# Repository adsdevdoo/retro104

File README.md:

# retro104

Платы расширения **PC/104** (шина ISA 8/16 бит) для ретро-одноплатников. Первый хост —
Advantech **PCM-3860/64 Rev.A1** с видеоконтроллером C&T F65545, то есть вариант **PCM-3864**
(386SX-40, плата 145 × 102 мм с разъёмами PC/104 CN1/CN2).

| pc104-audio — звуковая карта | pc104-blank — механическая ответка |
|---|---|
|  |  |

| Этап | Плата | Состояние |
|---|---|---|
| 1 | [`pc104-blank`](hardware/pc104-blank/) — пустая механическая ответка | **rev A: ERC 0, DRC 0, контакты сверены 104/104, Gerber проверены. Не изготовлена** |
| 2 | [`pc104-audio`](hardware/pc104-audio/) — звуковая карта на ESS ES1868F (донор BTC 1853L) | **rev A: ERC 0, нетлист сверен, разведена, DRC 0, Gerber проверены. Не изготовлена** |
| 3 | Ethernet | не начата |

**Статус: инженерные прототипы, не изготавливались и в железе не проверялись.**
Заказ, оплату и загрузку файлов в JLCPCB выполняет владелец. Изменения плат по ревизиям —
[CHANGELOG.md](CHANGELOG.md).

## pc104-audio — звуковая карта

Модуль PC/104 16 бит на **ESS ES1868F** с донорской карты BTC 1853L: Sound Blaster Pro 3.01,
FM-синтез ESFM (совместим с OPL3 по регистрам), MPU-401 UART и game port. Схема повторяет типовое
включение ESS (даташит ES1868, прил. B) с решениями владельца ([audio-options.md](docs/audio-options.md)).

- **Звук:** линейный выход, линейный вход, микрофон — гнёзда 3.5 мм Same Sky SJ1-3523N на верхнем
  крае, который при установке смотрит в сторону COM1 хоста. Усилителя нет.
- **Game/MIDI:** угловой IDC 2 × 8 на нижнем крае под стандартный кабель с планкой DB-15
  (раскладка National AN-1130). Вертикальный разъём с кабелем не проходит по высоте PC/104.
- **С донора:** ES1868F, EEPROM 93C66 (в панели, данные PnP) и при желании 74LS138. Кварц
  14.31818 МГц — низкий HC-49/S; донорский HC-49/U ставится только лёжа.
- **Питание:** только +5 В шины, аналоговая часть — через феррит.

| ES1868 | IRQA | IRQB | IRQC | IRQD | IRQE | IRQF | DRQA | DRQB | DRQC | DRQD |
|---|---|---|---|---|---|---|---|---|---|---|
| Линия ISA | 9 | 5 | 7 | 10 | 11 | 12 | 0 | 1 | 3 | 5 |

Раскладка — как у ESS и в EEPROM типовых карт, поэтому 93C66 донора подходит без перепрошивки.
Рекомендуемые ресурсы на PCM-3864: SB 220h / IRQ5 / DMA1, MPU-401 330h, FM 388h, джойстик 201h;
LPT хоста — на IRQ7. Подробно — [docs/pc104-audio.md](docs/pc104-audio.md).

<details>
<summary>Низ платы: название, таблицы IRQ/DRQ и ресурсов, перемычки, выводы J4 на шелкографии</summary>

</details>

Плата 95.89 × 90.17 мм, 2 слоя. Сигналы 0.25 мм, питание 0.4 мм, земля залита с двух сторон и
сшита. Трассировка — FreeRouting 2.5.0. На шелкографии верха обозначения всех деталей, у микросхем,
кварца и электролитов — номиналы. Архив для заказа:
[hardware/pc104-audio/fabrication/](hardware/pc104-audio/fabrication/).

## pc104-blank — механическая ответка

Электрически пустой модуль PC/104: только площадки разъёмов CN1/CN2 и четыре крепёжных отверстия.
На нём проверяются габарит, отверстия, ориентация и сопряжение разъёмов с PCM-3864. Контур,
отверстия и CN1/CN2 звуковой карты взяты отсюда.

| Параметр | CN2 | CN1 |
|---|---|---|
| По стандарту PC/104 | J1/P1, ряды A/B, контакты 1–32 | J2/P2, ряды C/D, контакты 0–19 |
| На PCM-3864 (с. 67 руководства) | CN2, 64 контакта | CN1, 40 контактов («Row A/B» = C/D) |
| Разъём | Samtec **ESQ-132-39-G-D** | Samtec **ESQ-120-39-G-D** |
| Тип | проходной (stackthrough): гнездо сверху, штыри снизу | то же |
| Корпус над платой / штырь под корпусом | 11.05 мм / 12.19 мм, квадрат 0.64 мм | то же |
| Отверстие / площадка | 1.02 мм (Samtec ESQ-SDT) / 1.70 мм | то же |
| Pin 1 (квадратная площадка, стрелка) | A1 | C0 |
| Положение, PC/104 рис. 3 | A: X 0.400 in, B: X 0.500 in; A1 в Y 0.250 in | C: X 0.300 in, D: X 0.200 in; C0 в Y 1.050 in |
| Ключевая позиция стандарта | B10 (у Advantech — GND) | C19 (у Advantech — N/C) |

Плата 3.775 × 3.550 in (95.89 × 90.17 мм), отверстия Ø3.18 мм с площадкой Ø6.35 мм:
(0.200; 0.200), (0.200; 3.350), (3.575; 0.350), (3.575; 3.250) in.

**Переходник не нужен.** Разъёмы PCM-3864 — гнёзда (руководство с. 58–59), а у модулей retro104 снизу
штыри проходных разъёмов. Переходник «male-male» Advantech нужен только модулю, у которого снизу тоже
гнёзда. Конец разъёмов с pin 32 / pin 19 при установке смотрит в сторону COM1 хоста.

| Верх | Сопряжение с гнёздами хоста (иллюстративные модели) |
|---|---|
|  |  |

## Документация

| Файл | Что внутри |
|---|---|
| [docs/pc104-audio.md](docs/pc104-audio.md) | звуковая карта: схема, IRQ/DMA, разъём game/MIDI, проверки, первая настройка |
| [docs/audio-options.md](docs/audio-options.md) | варианты звуковой карты, донор BTC 1853L, решения владельца |
| [docs/pc104-audio-schematic.pdf](docs/pc104-audio-schematic.pdf), [docs/pc104-audio-assembly.pdf](docs/pc104-audio-assembly.pdf) | схема и сборочный чертёж звуковой карты |
| [docs/mechanics.md](docs/mechanics.md) | механика PC/104 со ссылками на страницы, неоднозначности руководства, сверка с фото, переходник |
| [hardware/pc104-blank/reports/pinout-check.md](hardware/pc104-blank/reports/pinout-check.md) | все 104 контакта: координаты, PC/104 v2.6 и Advantech |
| [docs/pc104-blank-schematic.pdf](docs/pc104-blank-schematic.pdf) | схема ответки (все выводы не подключены) |
| [docs/manufacturing.md](docs/manufacturing.md) | заказ обеих плат в JLCPCB, что проверено и что нет |
| [docs/models.md](docs/models.md) | 3D-модели и их ограничения |
| [docs/sources.md](docs/sources.md) | документы, фото, открытые проекты, лицензионные пометки |
| [CHANGELOG.md](CHANGELOG.md) | изменения плат по ревизиям: медь, шелкография, файлы производства |

Документы производителей лежат в [docs/datasheets/](docs/datasheets/), фото хоста и донора — в
[docs/references/photos/](docs/references/photos/).

## Открыть и пересобрать

Нужен **KiCad 9.0.2 или новее**. Проекты: `hardware/pc104-audio/pc104-audio.kicad_pro` и
`hardware/pc104-blank/pc104-blank.kicad_pro`. Символы, футпринты и 3D-модели общие: `hardware/lib/`.

Схемы, платы, отчёты, рендеры, Gerber и проверки генерируются скриптами:

```bash
python tools/make_all.py
```

Без флагов звуковая карта не перетрассируется: разводка FreeRouting от запуска к запуску может
отличаться. Полная перестройка с FreeRouting 2.5.0 (jar лежит вне репозитория, `../tools/`):

```bash
python tools/make_all.py --route-audio
```

- Механика и таблицы сигналов PC/104 — `tools/pc104_data.py`, у каждой цифры ссылка на страницу.
- Детали и цепи звуковой карты — `tools/audio_design.py`, из него строятся схема, плата и проверки.
- Независимые проверки плат и файлов производства — `tools/check_board.py`,
  `tools/check_audio_netlist.py`, `tools/check_audio_board.py`.

## Структура

```
docs/        документация, datasheets/, references/photos/
hardware/    lib/ (общие символы, футпринты, 3D), pc104-blank/, pc104-audio/ (проекты, reports/, fabrication/)
images/      CAD-рендеры
tools/       генераторы и проверки
```

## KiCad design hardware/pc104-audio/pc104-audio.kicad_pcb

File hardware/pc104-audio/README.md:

# pc104-audio rev A

Звуковая карта PC/104 на ESS ES1868F (этап 2). Описание схемы, ресурсов и разъёмов —
[docs/pc104-audio.md](../../docs/pc104-audio.md). Проект для **KiCad 9.0.2 или новее**:
откройте `pc104-audio.kicad_pro`.

| Файл | Что это |
|---|---|
| `pc104-audio.kicad_sch` | схема, один лист A2: каждый вывод с меткой цепи, неиспользуемые — с флагом NC |
| `pc104-audio.kicad_pcb` | плата 95.89 × 90.17 мм, 2 слоя, разведена FreeRouting 2.5.0, GND залит с двух сторон |
| `../lib/` | общая библиотека: символы, футпринты (свои и копии KiCad 9), 3D-модели |
| `reports/erc.rpt`, `reports/drc.rpt` | ERC и DRC с проверкой соответствия схеме |
| `reports/netlist-check.txt` | нетлист против `tools/audio_design.py` |
| `reports/fab-check.md` | контур, CN1/CN2 и отверстия по стандарту, сверловка против платы |
| `fabrication/` | Gerber, Excellon, карты сверловки, архив для JLCPCB, `SHA256SUMS` |
| `../../docs/pc104-audio-assembly.pdf` | сборочный чертёж: верхняя шелкография и слой F.Fab (контуры корпусов) |

Статус: **ERC 0; нетлист = `audio_design.py`; FreeRouting — 0 неразведённых; DRC 0 нарушений,
0 неподключённых, 0 ошибок футпринтов; файлы производства проверены. В железе не проверялась.**

Как получена плата:

1. `tools/audio_design.py` — детали, цепи и неподключённые выводы.
2. `tools/gen_audio.py` — схема; `kicad-cli sch export netlist` — нетлист.
3. `tools/check_audio_netlist.py` — нетлист против `audio_design.py`.
4. `tools/build_audio_board.py` — расстановка и DSN.
5. FreeRouting 2.5.0 — трассировка.
6. `tools/route_audio_board.py` — импорт трассировки, земля, сшивка.
7. `tools/audio_silk.py` — шелкография обеих сторон.

Всё это делает `python tools/make_all.py --route-audio`. Без флага плата не перетрассируется:
выполняется только шаг 7, затем проверки и выгрузка. Шаг 7 меняет только шелкографию и при повторном
запуске даёт тот же файл.

Шелкография:

- **Верх.** Обозначения всех деталей, 1.0 мм. У микросхем, кварца и электролитов указан номинал:
  ES1868F, 74HCT138, 93C66, 14.318MHz, 10u/47u. Место для подписи скрипт ищет сам: не ближе
  0.2 мм к площадкам и другой шелкографии, не на чужих корпусах, не ближе 0.5 мм к краю. Номиналы
  0805 — в схеме.
- **Низ.** Рамка с названием. Таблица соответствия линий IRQ/DRQ ES1868 линиям ISA. Типовые ресурсы
  PnP. Назначение перемычек JP1/JP2. Сведения о гнёздах. Названия выводов J4 у каждой площадки.
  Подписи CN1/CN2 и ссылка на репозиторий.

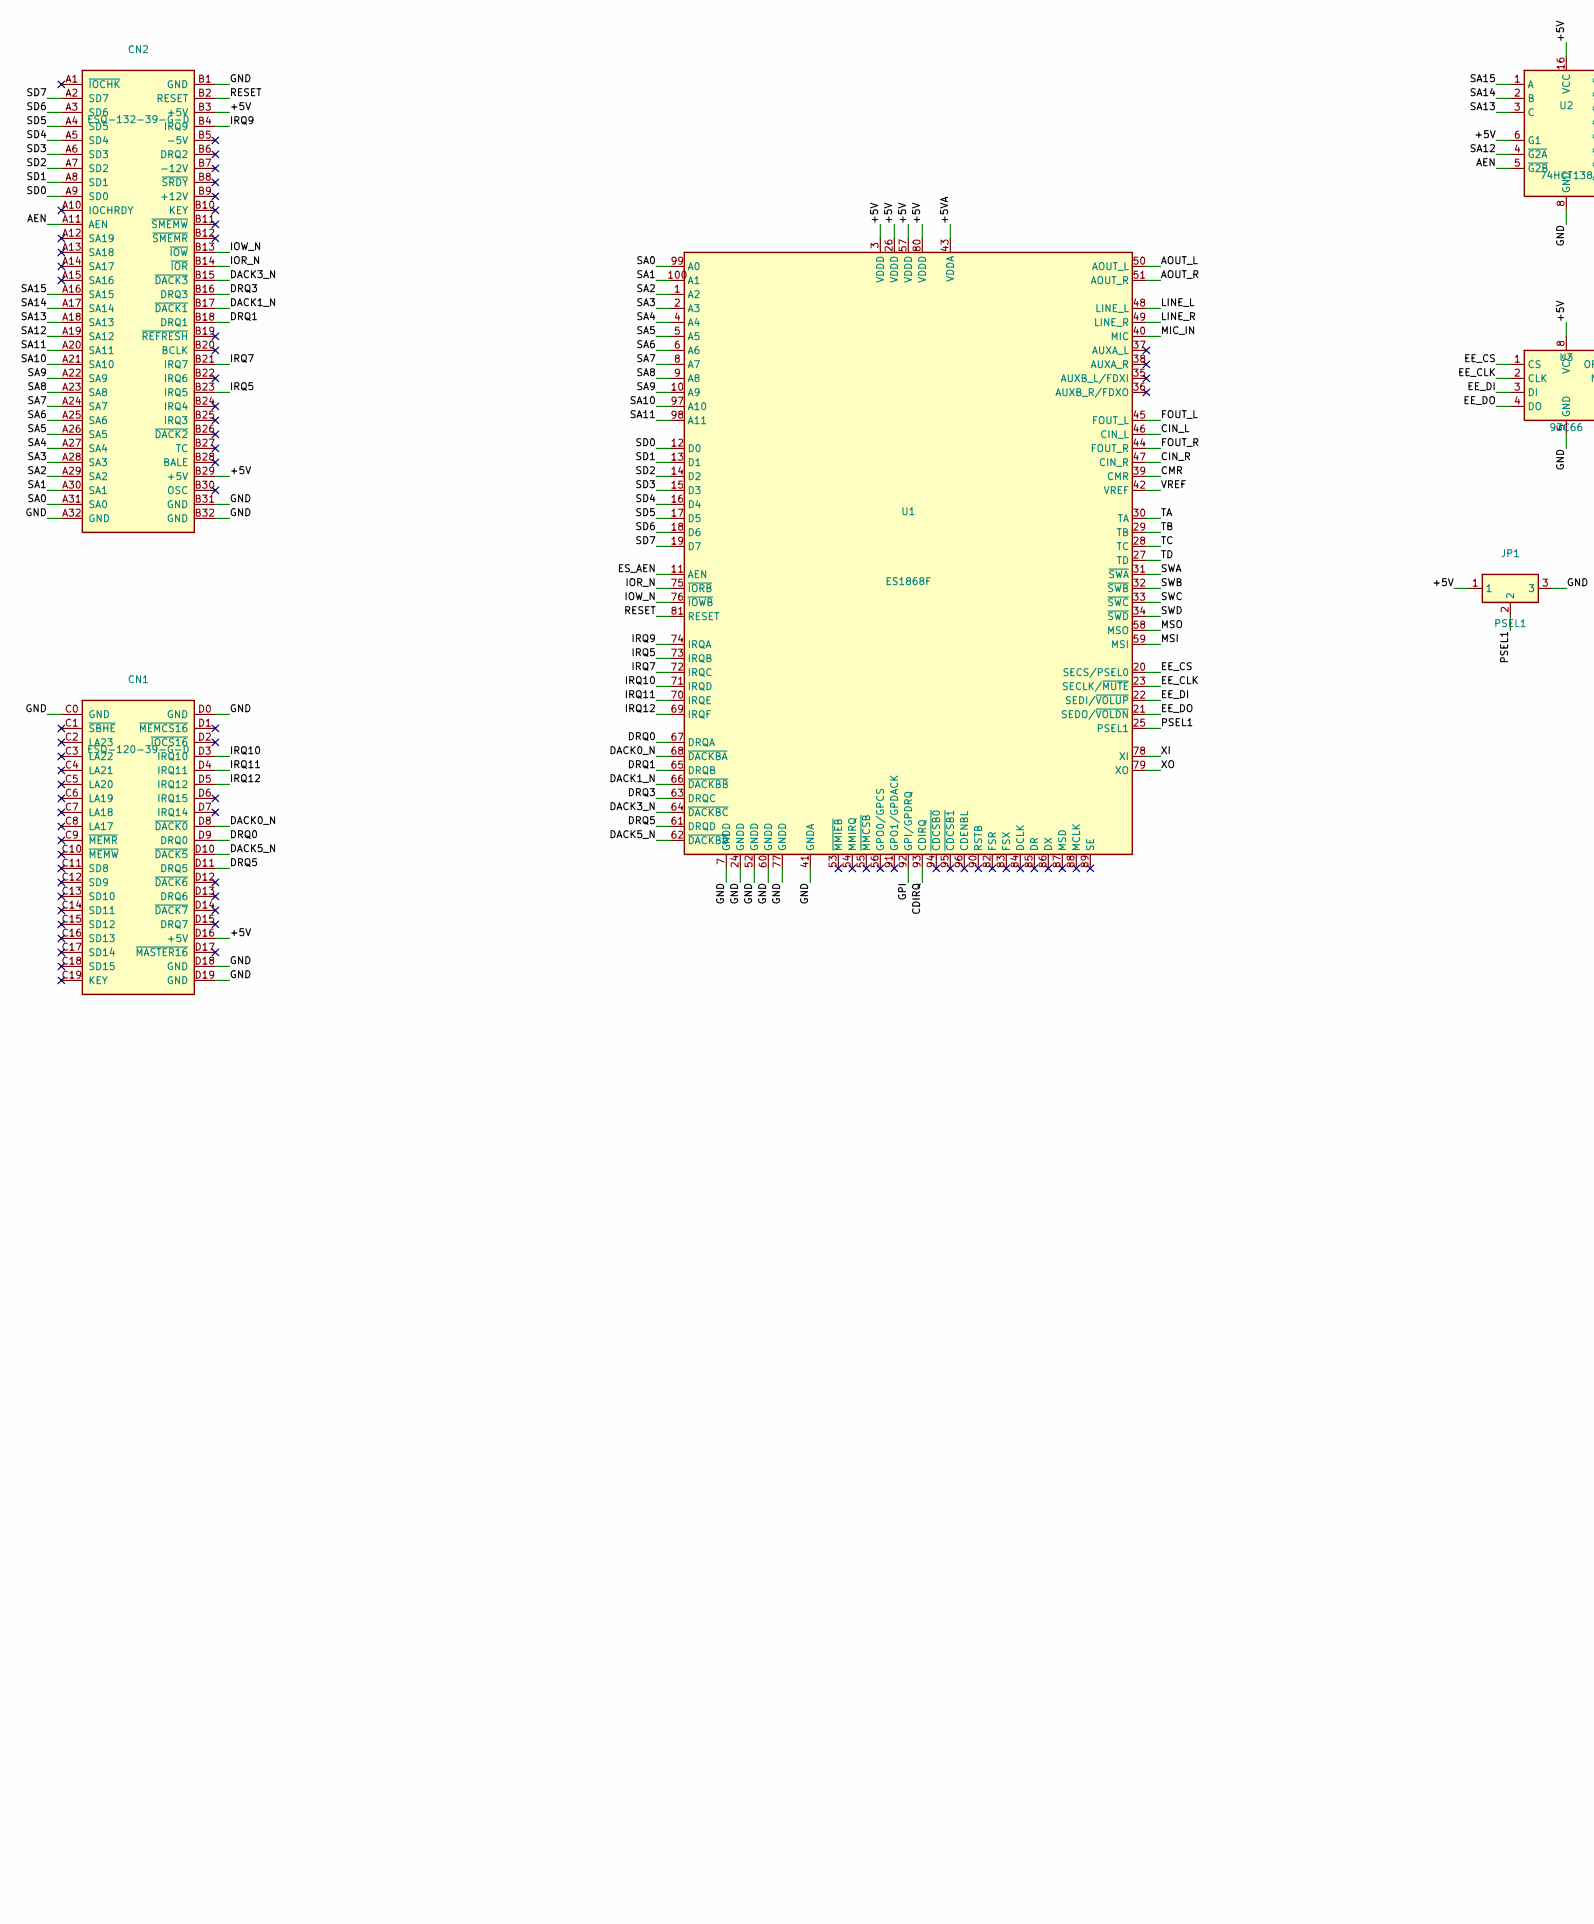
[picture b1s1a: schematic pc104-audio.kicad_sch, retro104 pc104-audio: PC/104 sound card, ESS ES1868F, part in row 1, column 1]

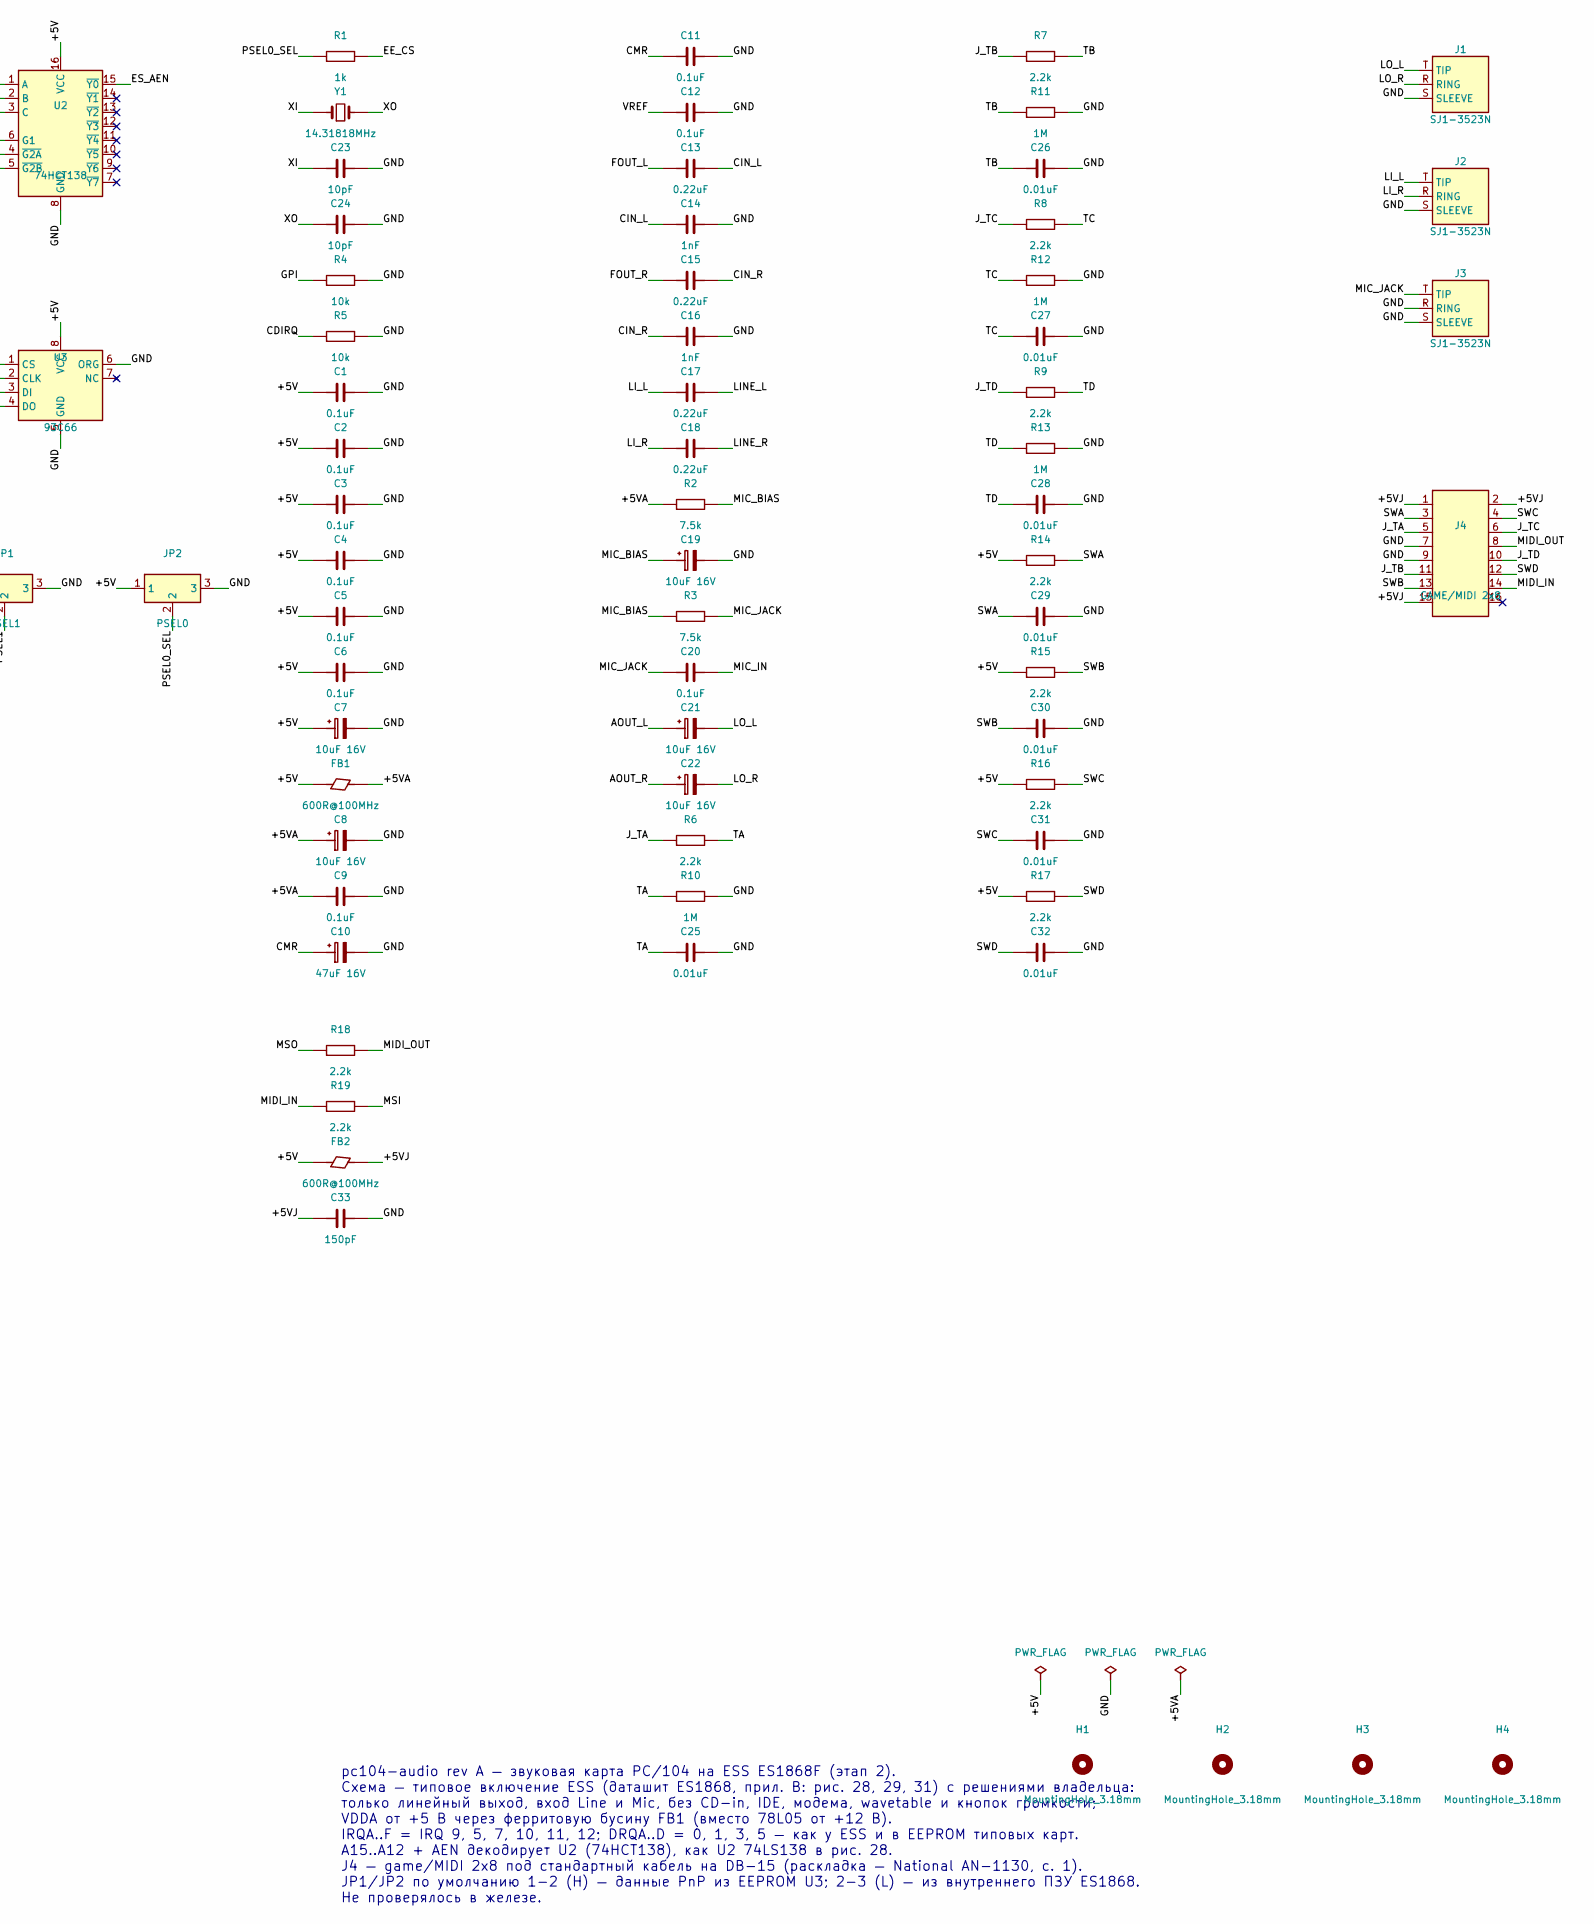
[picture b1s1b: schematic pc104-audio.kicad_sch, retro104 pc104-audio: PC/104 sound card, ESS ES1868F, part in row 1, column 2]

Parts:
C1, C2, C3, C4, C5, C6, C9, C11, C12, C20: 0.1uF; C_0805_2012Metric_Pad1.18x1.45mm_HandSolder
C7, C8, C19, C21, C22: 10uF 16V; CP_Elec_4x5.4
C10: 47uF 16V; CP_Elec_6.3x5.4
C13, C15, C17, C18: 0.22uF; C_0805_2012Metric_Pad1.18x1.45mm_HandSolder
C14, C16: 1nF; C_0805_2012Metric_Pad1.18x1.45mm_HandSolder
C23, C24: 10pF; C_0805_2012Metric_Pad1.18x1.45mm_HandSolder
C25, C26, C27, C28, C29, C30, C31, C32: 0.01uF; C_0805_2012Metric_Pad1.18x1.45mm_HandSolder
C33: 150pF; C_0805_2012Metric_Pad1.18x1.45mm_HandSolder
CN1: ESQ-120-39-G-D; PC104_J2P2_2x20_P2.54mm_Stackthrough; MPN Samtec ESQ-120-39-G-D
CN2: ESQ-132-39-G-D; PC104_J1P1_2x32_P2.54mm_Stackthrough; MPN Samtec ESQ-132-39-G-D
FB1, FB2: 600R@100MHz; L_0805_2012Metric_Pad1.15x1.40mm_HandSolder
H1, H2, H3, H4: MountingHole_3.18mm; PC104_MountingHole_3.18mm_Pad6.35mm
J1, J2, J3: SJ1-3523N; Jack_3.5mm_CUI_SJ1-3523N_Horizontal_Slots; MPN CUI/Same Sky SJ1-3523N
J4: GAME/MIDI 2x8; IDC-Header_2x08_P2.54mm_Horizontal; MPN 2x8 IDC box header, right angle, 2.54 mm
JP1: PSEL1; SolderJumper-3_P1.3mm_Bridged12_RoundedPad1.0x1.5mm
JP2: PSEL0; SolderJumper-3_P1.3mm_Bridged12_RoundedPad1.0x1.5mm
R1: 1k; R_0805_2012Metric_Pad1.20x1.40mm_HandSolder
R2, R3: 7.5k; R_0805_2012Metric_Pad1.20x1.40mm_HandSolder
R4, R5: 10k; R_0805_2012Metric_Pad1.20x1.40mm_HandSolder
R6, R7, R8, R9, R14, R15, R16, R17, R18, R19: 2.2k; R_0805_2012Metric_Pad1.20x1.40mm_HandSolder
R10, R11, R12, R13: 1M; R_0805_2012Metric_Pad1.20x1.40mm_HandSolder
U1: ES1868F; PQFP-100_14x20mm_P0.65mm; MPN ESS ES1868F
U2: 74HCT138; SOIC-16_3.9x9.9mm_P1.27mm; MPN TI SN74HCT138D
U3: 93C66; DIP-8_W7.62mm_Socket_LongPads; MPN Atmel AT93C66 (donor) in DIP-8 socket
Y1: 14.31818MHz; Crystal_HC49-4H_Vertical; MPN HC-49/S 14.31818 MHz, CL 18-20 pF

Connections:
/+5V: C1.1, C2.1, C3.1, C4.1, C5.1, C6.1, C7.1 (+), CN1.D16 (+5V), CN2.B3 (+5V), CN2.B29 (+5V), FB1.1, FB2.1, JP1.1, JP2.1, R14.1, R15.1, R16.1, R17.1, U1.3 (VDDD), U1.26 (VDDD), U1.57 (VDDD), U1.80 (VDDD), U2.6 (G1), U2.16 (VCC), U3.8 (VCC)
/+5VA: C8.1 (+), C9.1, FB1.2, R2.1, U1.43 (VDDA)
/+5VJ: C33.1, FB2.2, J4.1, J4.2, J4.15
/AEN: CN2.A11 (AEN), U2.5 (~G2B)
/AOUT_L: C21.1 (+), U1.50 (AOUT_L)
/AOUT_R: C22.1 (+), U1.51 (AOUT_R)
/CDIRQ: R5.1, U1.93 (CDIRQ)
/CIN_L: C13.2, C14.1, U1.46 (CIN_L)
/CIN_R: C15.2, C16.1, U1.47 (CIN_R)
/CMR: C10.1 (+), C11.1, U1.39 (CMR)
/DACK0_N: CN1.D8 (~DACK0), U1.68 (~DACKBA)
/DACK1_N: CN2.B17 (~DACK1), U1.66 (~DACKBB)
/DACK3_N: CN2.B15 (~DACK3), U1.64 (~DACKBC)
/DACK5_N: CN1.D10 (~DACK5), U1.62 (~DACKBD)
/DRQ0: CN1.D9 (DRQ0), U1.67 (DRQA)
/DRQ1: CN2.B18 (DRQ1), U1.65 (DRQB)
/DRQ3: CN2.B16 (DRQ3), U1.63 (DRQC)
/DRQ5: CN1.D11 (DRQ5), U1.61 (DRQD)
/EE_CLK: U1.23 (SECLK/~MUTE), U3.2 (CLK)
/EE_CS: R1.2, U1.20 (SECS/PSEL0), U3.1 (CS)
/EE_DI: U1.22 (SEDI/~VOLUP), U3.3 (DI)
/EE_DO: U1.21 (SEDO/~VOLDN), U3.4 (DO)
/ES_AEN: U1.11 (AEN), U2.15 (~Y0)
/FOUT_L: C13.1, U1.45 (FOUT_L)
/FOUT_R: C15.1, U1.44 (FOUT_R)
/GND: C1.2, C2.2, C3.2, C4.2, C5.2, C6.2, C7.2 (-), C8.2 (-), C9.2, C10.2 (-), C11.2, C12.2, C14.2, C16.2, C19.2 (-), C23.2, C24.2, C25.2, C26.2, C27.2, C28.2, C29.2, C30.2, C31.2, C32.2, C33.2, CN1.C0 (GND), CN1.D0 (GND), CN1.D18 (GND), CN1.D19 (GND), CN2.A32 (GND), CN2.B1 (GND), CN2.B31 (GND), CN2.B32 (GND), J1.S (SLEEVE), J2.S (SLEEVE), J3.R (RING), J3.S (SLEEVE), J4.7, J4.9, JP1.3, JP2.3, R4.2, R5.2, R10.2, R11.2, R12.2, R13.2, U1.7 (GNDD), U1.24 (GNDD), U1.41 (GNDA), U1.52 (GNDD), U1.60 (GNDD), U1.77 (GNDD), U2.8 (GND), U3.5 (GND), U3.6 (ORG)
/GPI: R4.1, U1.92 (GPI/GPDRQ)
/IOR_N: CN2.B14 (~IOR), U1.75 (~IORB)
/IOW_N: CN2.B13 (~IOW), U1.76 (~IOWB)
/IRQ5: CN2.B23 (IRQ5), U1.73 (IRQB)
/IRQ7: CN2.B21 (IRQ7), U1.72 (IRQC)
/IRQ9: CN2.B4 (IRQ9), U1.74 (IRQA)
/IRQ10: CN1.D3 (IRQ10), U1.71 (IRQD)
/IRQ11: CN1.D4 (IRQ11), U1.70 (IRQE)
/IRQ12: CN1.D5 (IRQ12), U1.69 (IRQF)
/J_TA: J4.5, R6.1
/J_TB: J4.11, R7.1
/J_TC: J4.6, R8.1
/J_TD: J4.10, R9.1
/LINE_L: C17.2, U1.48 (LINE_L)
/LINE_R: C18.2, U1.49 (LINE_R)
/LI_L: C17.1, J2.T (TIP)
/LI_R: C18.1, J2.R (RING)
/LO_L: C21.2 (-), J1.T (TIP)
/LO_R: C22.2 (-), J1.R (RING)
/MIC_BIAS: C19.1 (+), R2.2, R3.1
/MIC_IN: C20.2, U1.40 (MIC)
/MIC_JACK: C20.1, J3.T (TIP), R3.2
/MIDI_IN: J4.14, R19.1
/MIDI_OUT: J4.8, R18.2
/MSI: R19.2, U1.59 (MSI)
/MSO: R18.1, U1.58 (MSO)
/PSEL0_SEL: JP2.2, R1.1
/PSEL1: JP1.2, U1.25 (PSEL1)
/RESET: CN2.B2 (RESET), U1.81 (RESET)
/SA0: CN2.A31 (SA0), U1.99 (A0)
/SA1: CN2.A30 (SA1), U1.100 (A1)
/SA2: CN2.A29 (SA2), U1.1 (A2)
/SA3: CN2.A28 (SA3), U1.2 (A3)
/SA4: CN2.A27 (SA4), U1.4 (A4)
/SA5: CN2.A26 (SA5), U1.5 (A5)
/SA6: CN2.A25 (SA6), U1.6 (A6)
/SA7: CN2.A24 (SA7), U1.8 (A7)
/SA8: CN2.A23 (SA8), U1.9 (A8)
/SA9: CN2.A22 (SA9), U1.10 (A9)
/SA10: CN2.A21 (SA10), U1.97 (A10)
/SA11: CN2.A20 (SA11), U1.98 (A11)
/SA12: CN2.A19 (SA12), U2.4 (~G2A)
/SA13: CN2.A18 (SA13), U2.3 (C)
/SA14: CN2.A17 (SA14), U2.2 (B)
/SA15: CN2.A16 (SA15), U2.1 (A)
/SD0: CN2.A9 (SD0), U1.12 (D0)
/SD1: CN2.A8 (SD1), U1.13 (D1)
/SD2: CN2.A7 (SD2), U1.14 (D2)
/SD3: CN2.A6 (SD3), U1.15 (D3)
/SD4: CN2.A5 (SD4), U1.16 (D4)
/SD5: CN2.A4 (SD5), U1.17 (D5)
/SD6: CN2.A3 (SD6), U1.18 (D6)
/SD7: CN2.A2 (SD7), U1.19 (D7)
/SWA: C29.1, J4.3, R14.2, U1.31 (~SWA)
/SWB: C30.1, J4.13, R15.2, U1.32 (~SWB)
/SWC: C31.1, J4.4, R16.2, U1.33 (~SWC)
/SWD: C32.1, J4.12, R17.2, U1.34 (~SWD)
/TA: C25.1, R6.2, R10.1, U1.30 (TA)
/TB: C26.1, R7.2, R11.1, U1.29 (TB)
/TC: C27.1, R8.2, R12.1, U1.28 (TC)
/TD: C28.1, R9.2, R13.1, U1.27 (TD)
/VREF: C12.1, U1.42 (VREF)
/XI: C23.1, U1.78 (XI), Y1.1
/XO: C24.1, U1.79 (XO), Y1.2

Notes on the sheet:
pc104-audio rev A — звуковая карта PC/104 на ESS ES1868F (этап 2). Схема — типовое включение ESS (даташит ES1868, прил. B: рис. 28, 29, 31) с решениями владельца: только линейный выход, вход Line и Mic, без CD-in, IDE, модема, wavetable и кнопок громкости; VDDA от +5 В через ферритовую бусину FB1 (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

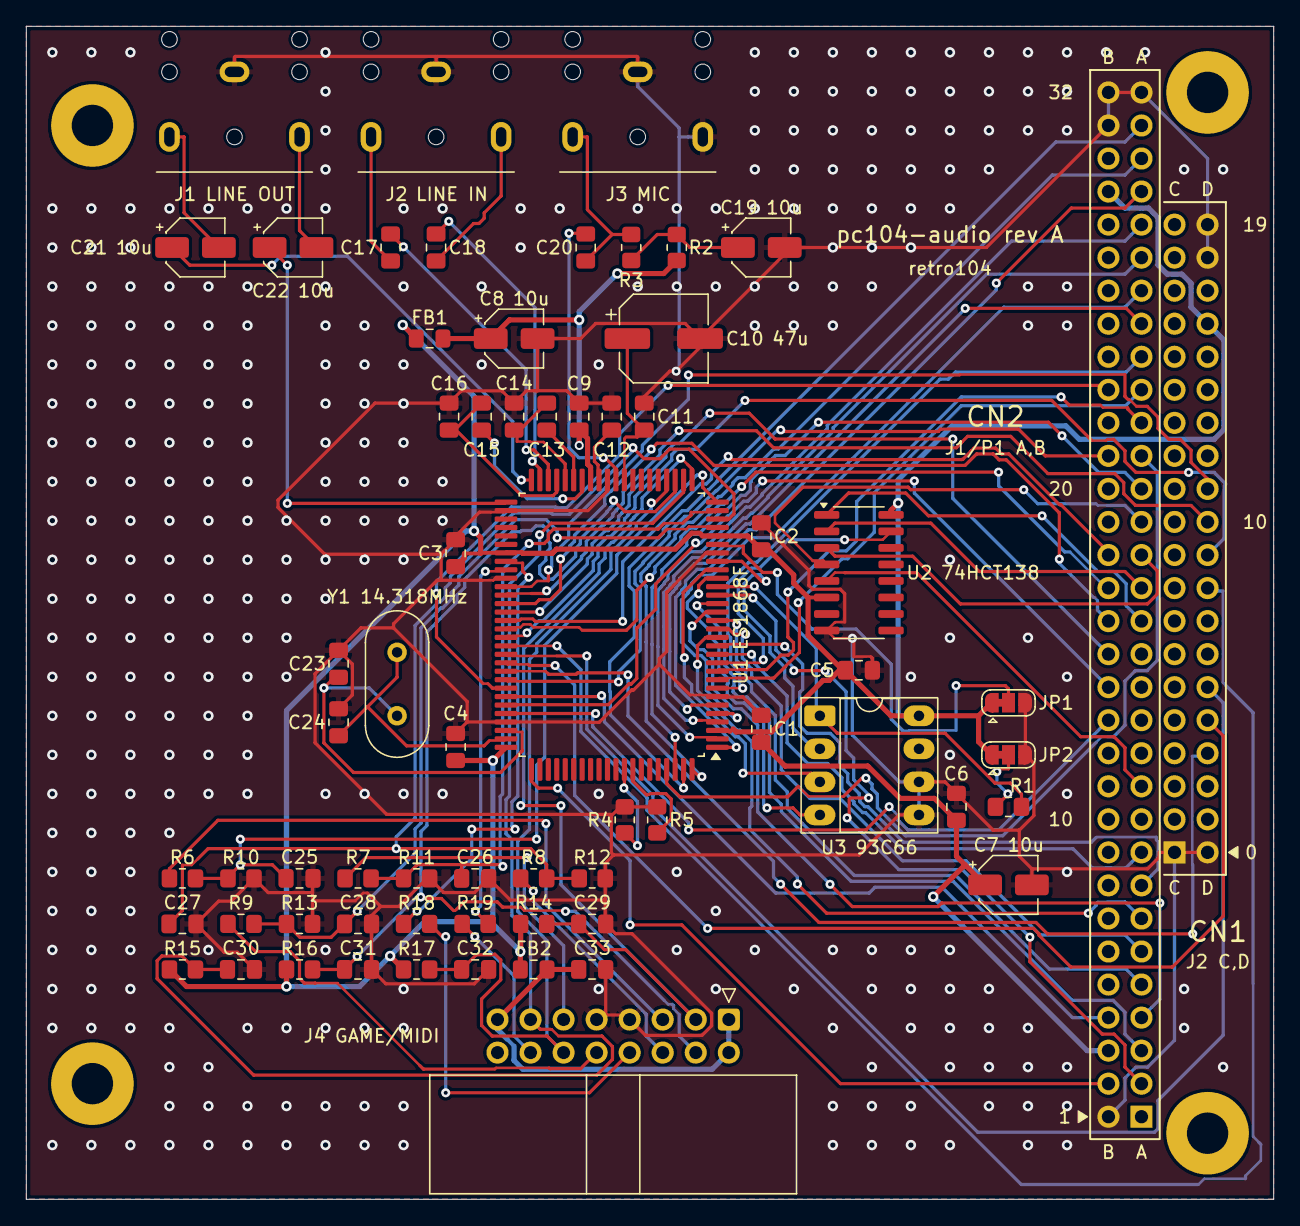
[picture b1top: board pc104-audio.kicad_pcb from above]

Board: 2 copper layers, 95.9 x 90.2 mm, 70 parts (0 on the bottom side), 90 nets.

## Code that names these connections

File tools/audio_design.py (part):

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}
for pin, net in U1.items():
    c(net, "U1.%d" % pin)
# Not used (left open in ESS Fig. 28 as well): AUX inputs (internal pull-ups to CMR), modem pins,
# DSP serial interface and wavetable inputs (internal pull-downs), CD-ROM chip selects, GPO0/GPO1, RSTB.
for pin in (35, 36, 37, 38, 53, 54, 55, 56, 82, 83, 84, 85, 86, 87, 88, 89, 90, 91, 94, 95, 96):
    NC.append(("U1", str(pin)))
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
# ------------------------------------------------------------------ address decode, EEPROM, crystal
part("U2", "74HCT138", "74HCT138", mpn="TI SN74HCT138D", note="donor has 74LS138, either works")
for pin, net in {1: "SA15", 2: "SA14", 3: "SA13", 4: "SA12", 5: "AEN", 6: "+5V", 15: "ES_AEN",
                 16: "+5V", 8: "GND"}.items():
    c(net, "U2.%d" % pin)
for pin in (14, 13, 12, 11, 10, 9, 7):
    NC.append(("U2", str(pin)))

part("U3", "93C66", "93C66", mpn="Atmel AT93C66 (donor) in DIP-8 socket", note="PnP resource EEPROM, ORG=GND (x8)")
for pin, net in {1: "EE_CS", 2: "EE_CLK", 3: "EE_DI", 4: "EE_DO", 5: "GND", 6: "GND", 8: "+5V"}.items():
    c(net, "U3.%d" % pin)
NC.append(("U3", "7"))

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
